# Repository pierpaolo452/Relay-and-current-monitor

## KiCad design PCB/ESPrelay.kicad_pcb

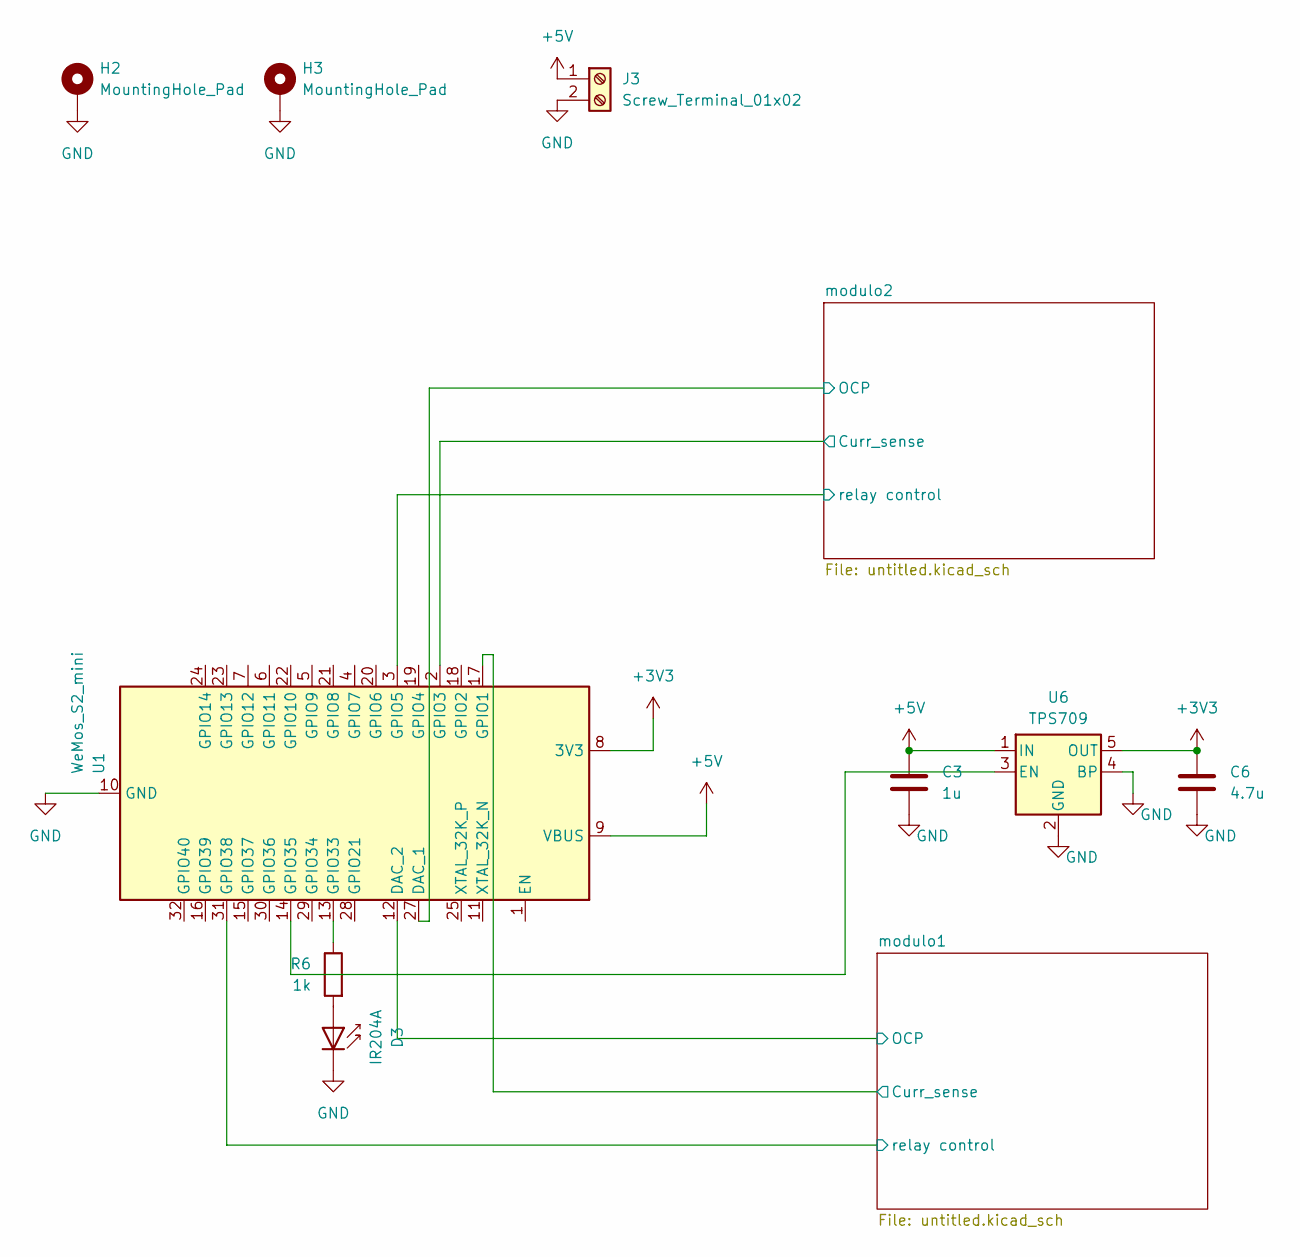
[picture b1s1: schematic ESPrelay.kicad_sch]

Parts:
C3: 1u; C_0805_2012Metric_Pad1.18x1.45mm_HandSolder
C6: 4.7u; C_0805_2012Metric_Pad1.18x1.45mm_HandSolder
D3: IR204A; LED_D3.0mm_Horizontal_O1.27mm_Z2.0mm_IRBlack
H2, H3: MountingHole_Pad; MountingHole_5.3mm_M5_Pad_Via
J3: Screw_Terminal_01x02; TerminalBlock_Phoenix_MKDS-3-2-5.08_1x02_P5.08mm_Horizontal
R6: 1k; R_0805_2012Metric
U1: WeMos_S2_mini; WEMOS_S2_mini
U6: TPS709; SOT-23-5_HandSoldering

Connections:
+3V3: C6.1, U1.8 (3V3), U6.5 (OUT); also elsewhere on the board
+5V: C3.1, J3.1, U1.9 (VBUS), U6.1 (IN); also elsewhere on the board
/modulo1/Curr_sense: U1.17 (GPIO1); also elsewhere on the board
/modulo1/OCP: U1.12 (DAC_2); also elsewhere on the board
/modulo1/relay control: U1.31 (GPIO38); also elsewhere on the board
/modulo2/Curr_sense: U1.2 (GPIO3); also elsewhere on the board
/modulo2/OCP: U1.27 (DAC_1); also elsewhere on the board
/modulo2/relay control: U1.3 (GPIO5); also elsewhere on the board
GND: C3.2, C6.2, D3.1 (K), H2.1, H3.1, J3.2, U1.10 (GND), U1.26 (GND), U6.2 (GND), U6.4 (BP); also elsewhere on the board
unnamed: D3.2 (A), R6.2
unnamed: R6.1, U1.13 (GPIO33)
unnamed: U1.14 (GPIO35), U6.3 (EN)

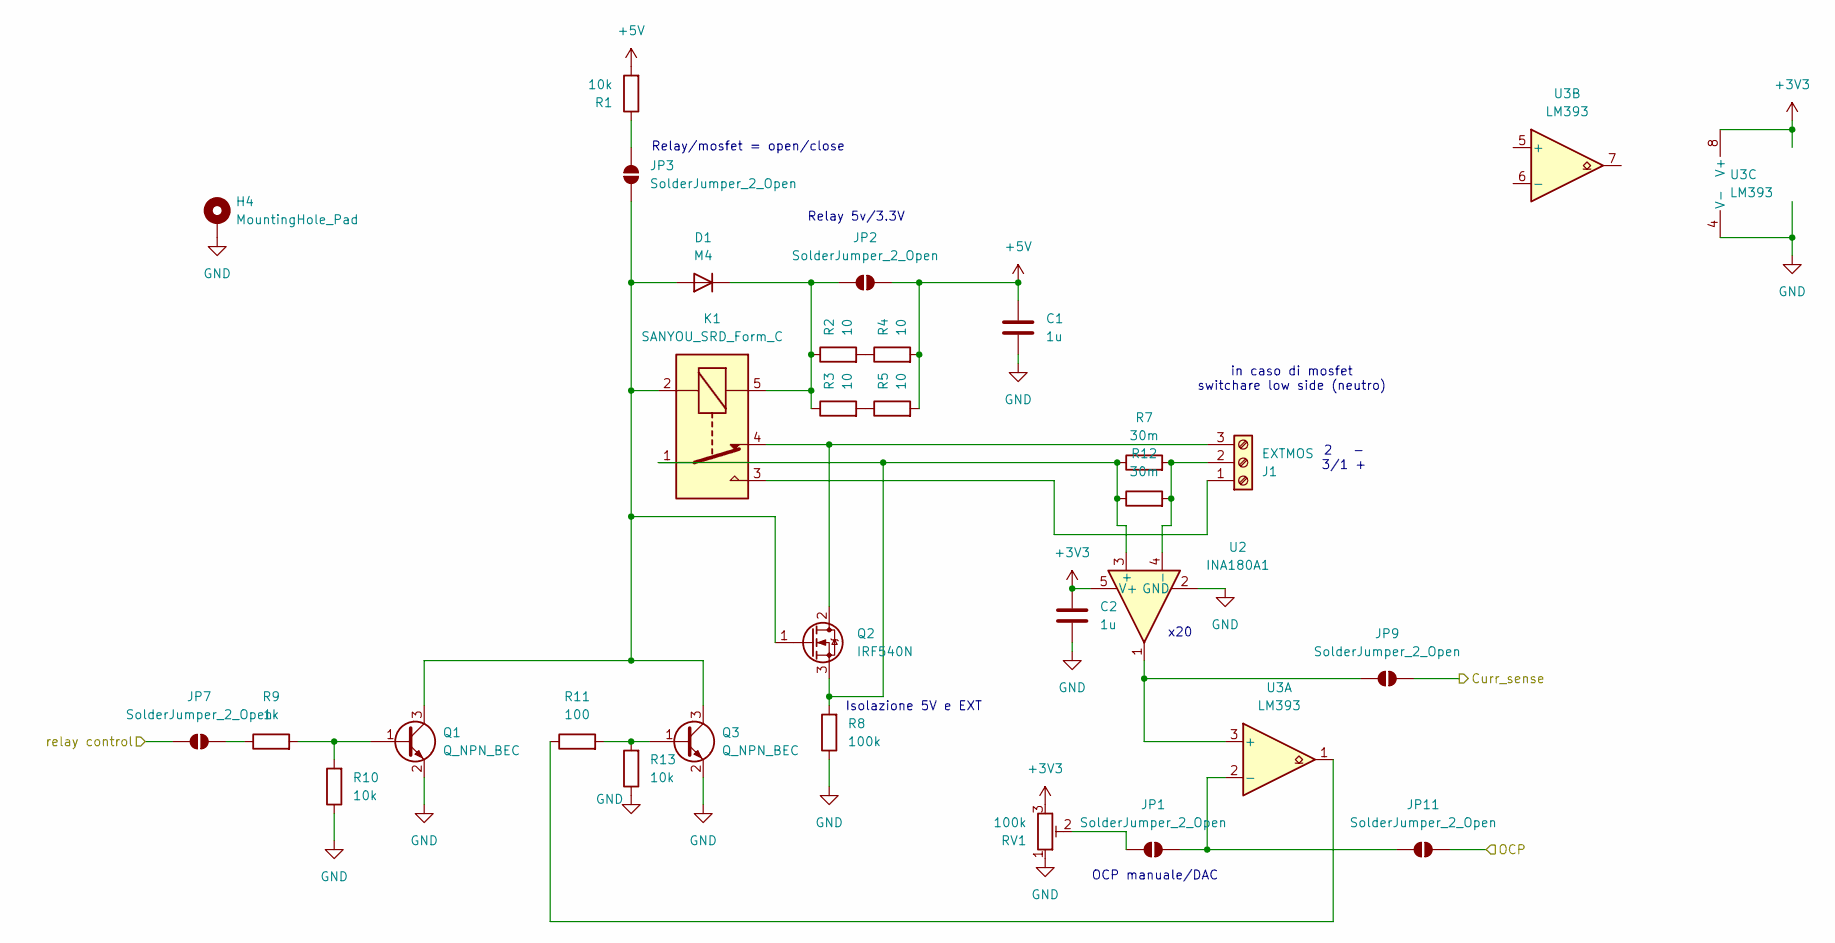
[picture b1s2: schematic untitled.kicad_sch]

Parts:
C1, C2: 1u; C_0805_2012Metric
D1: M4; D_SMA
H4: MountingHole_Pad; MountingHole_5.3mm_M5_Pad_Via
J1: EXTMOS; TerminalBlock_Phoenix_MKDS-1,5-3-5.08_1x03_P5.08mm_Horizont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
JP1, JP2, JP3, JP7, JP9, JP11: SolderJumper_2_Open; SolderJumper-2_P1.3mm_Open_RoundedPad1.0x1.5mm
K1: SANYOU_SRD_Form_C; Relay_SPDT_SANYOU_SRD_Series_Form_C
Q1, Q3: Q_NPN_BEC; SOT-23
Q2: IRF540N; TO-220-3_Vertical
R1, R10, R13: 10k; R_0805_2012Metric
R2, R3, R4, R5: 10; R_0805_2012Metric
R7, R12: 30m; R_2512_6332Metric_Pad1.40x3.35mm_HandSolder
R8: 100k; R_0805_2012Metric
R9: 1k; R_0805_2012Metric
R11: 100; R_0805_2012Metric
RV1: 100k; Potentiometer_ACP_CA9-H5_Horizontal; LCSC C118929
U2: INA180A1; SOT-23-5
U3: LM393; SOIC-8_3.9x4.9mm_P1.27mm

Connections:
+3V3: C2.1, RV1.3, U2.5 (V+), U3.8 (V+); also elsewhere on the board
+5V: C1.1, JP2.1 (A), R1.2, R4.2, R5.2; also elsewhere on the board
/modulo1/Curr_sense: JP9.1 (A); also elsewhere on the board
/modulo1/OCP: JP11.1 (A); also elsewhere on the board
/modulo1/relay control: JP7.2 (B); also elsewhere on the board
GND: C1.2, C2.2, H4.1, Q1.2 (E), Q3.2 (E), R8.1, R10.1, R13.1, RV1.1, U2.2 (GND), U3.4 (V-); also elsewhere on the board
unnamed: D1.2 (A), JP3.1 (A), K1.2, Q1.3 (C), Q2.1 (G), Q3.3 (C)
unnamed: D1.1 (K), JP2.2 (B), K1.5, R2.1, R3.1
unnamed: J1.1, K1.3
unnamed: J1.2, R7.2, R12.2, U2.4 (-)
unnamed: J1.3, K1.4, Q2.2 (D)
unnamed: JP1.1 (A), JP11.2 (B), U3.2 (-)
unnamed: JP1.2 (B), RV1.2
unnamed: JP3.2 (B), R1.1
unnamed: JP7.1 (A), R9.1
unnamed: JP9.2 (B), U2.1, U3.3 (+)
unnamed: Q1.1 (B), R9.2, R10.2
unnamed: K1.1, Q2.3 (S), R7.1, R8.2, R12.1, U2.3 (+)
unnamed: Q3.1 (B), R11.2, R13.2
unnamed: R2.2, R4.1
unnamed: R3.2, R5.1
unnamed: R11.1, U3.1

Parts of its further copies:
C4, C5: 1u; C_0805_2012Metric
D2: M4; D_SMA
H1: MountingHole_Pad; MountingHole_5.3mm_M5_Pad_Via
J2: EXTMOS; TerminalBlock_Phoenix_MKDS-1,5-3-5.08_1x03_P5.08mm_Horizont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
JP4, JP5, JP6, JP8, JP10, JP12: SolderJumper_2_Open; SolderJumper-2_P1.3mm_Open_RoundedPad1.0x1.5mm
K2: SANYOU_SRD_Form_C; Relay_SPDT_SANYOU_SRD_Series_Form_C
Q4, Q5: Q_NPN_BEC; SOT-23
Q6: IRF540N; TO-220-3_Vertical
R14: 1k; R_0805_2012Metric
R15, R17, R18: 10k; R_0805_2012Metric
R16: 100; R_0805_2012Metric
R19: 100k; R_0805_2012Metric
R20, R21, R22, R23: 10; R_0805_2012Metric
R24, R25: 30m; R_2512_6332Metric_Pad1.40x3.35mm_HandSolder
RV2: 100k; Potentiometer_ACP_CA9-H5_Horizontal; LCSC C118929
U4: INA180A1; SOT-23-5
U5: LM393; SOIC-8_3.9x4.9mm_P1.27mm

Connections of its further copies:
+3V3: C5.1, RV2.3, U4.5 (V+), U5.8 (V+); also elsewhere on the board
+5V: C4.1, JP5.1 (A), R17.2, R22.2, R23.2; also elsewhere on the board
/modulo2/Curr_sense: JP10.1 (A); also elsewhere on the board
/modulo2/OCP: JP12.1 (A); also elsewhere on the board
/modulo2/relay control: JP8.2 (B); also elsewhere on the board
GND: C4.2, C5.2, H1.1, Q4.2 (E), Q5.2 (E), R15.1, R18.1, R19.1, RV2.1, U4.2 (GND), U5.4 (V-); also elsewhere on the board
unnamed: D2.2 (A), JP4.1 (A), K2.2, Q4.3 (C), Q5.3 (C), Q6.1 (G)
unnamed: D2.1 (K), JP5.2 (B), K2.5, R20.1, R21.1
unnamed: J2.1, K2.3
unnamed: J2.2, R24.2, R25.2, U4.4 (-)
unnamed: J2.3, K2.4, Q6.2 (D)
unnamed: JP4.2 (B), R17.1
unnamed: JP6.2 (B), RV2.2
unnamed: JP8.1 (A), R14.1
unnamed: JP10.2 (B), U4.1, U5.3 (+)
unnamed: JP6.1 (A), JP12.2 (B), U5.2 (-)
unnamed: Q4.1 (B), R14.2, R15.2
unnamed: Q5.1 (B), R16.2, R18.2
unnamed: K2.1, Q6.3 (S), R19.2, R24.1, R25.1, U4.3 (+)
unnamed: R16.1, U5.1
unnamed: R20.2, R22.1
unnamed: R21.2, R23.1

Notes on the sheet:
x20
Isolazione 5V e EXT
in caso di mosfet switchare low side (neutro)
2 - 3/1 +
OCP manuale/DAC
Relay 5v/3.3V
Relay/mosfet = open/close

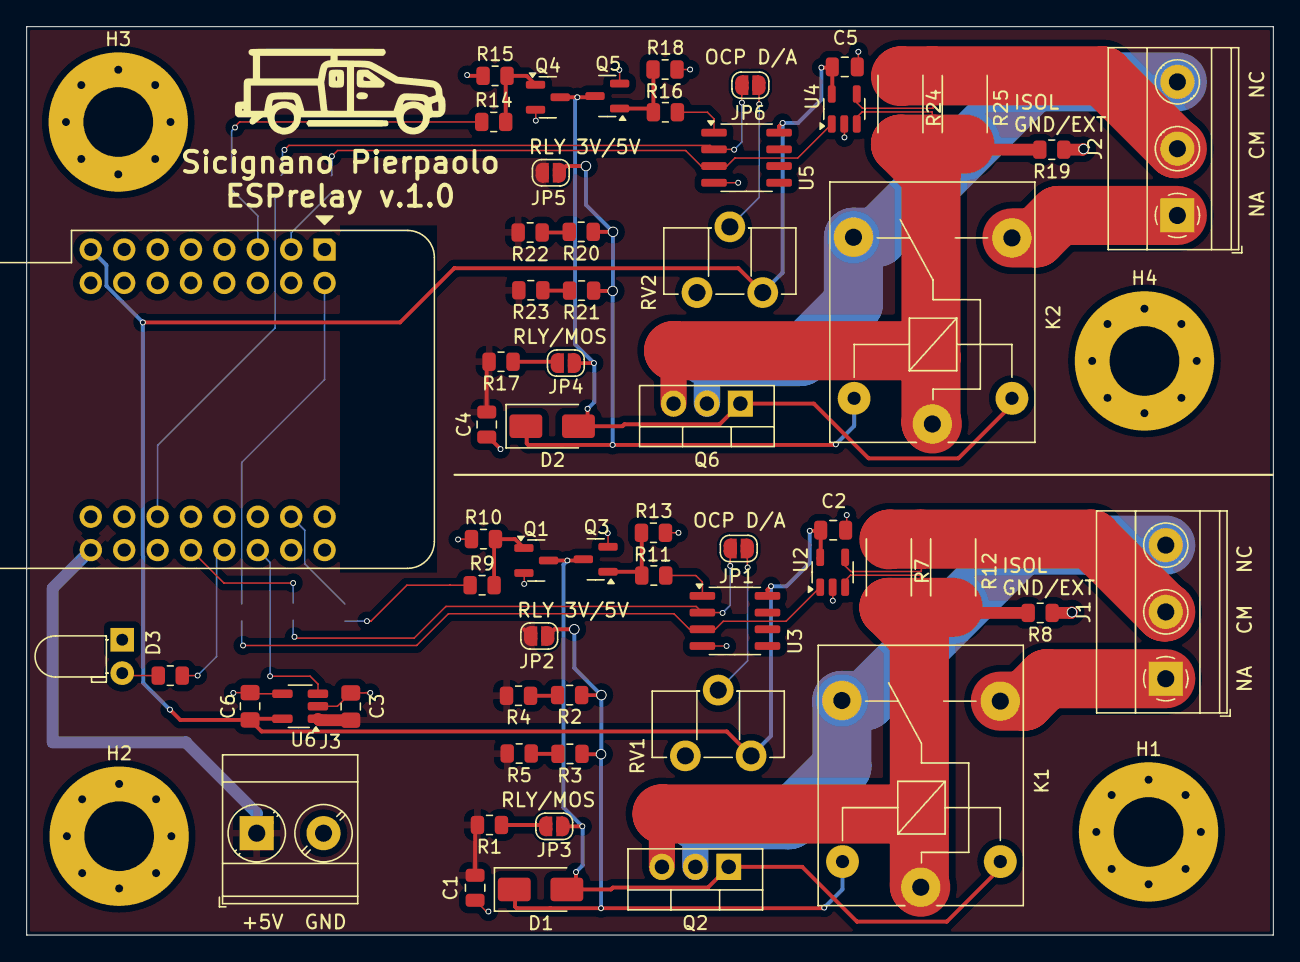
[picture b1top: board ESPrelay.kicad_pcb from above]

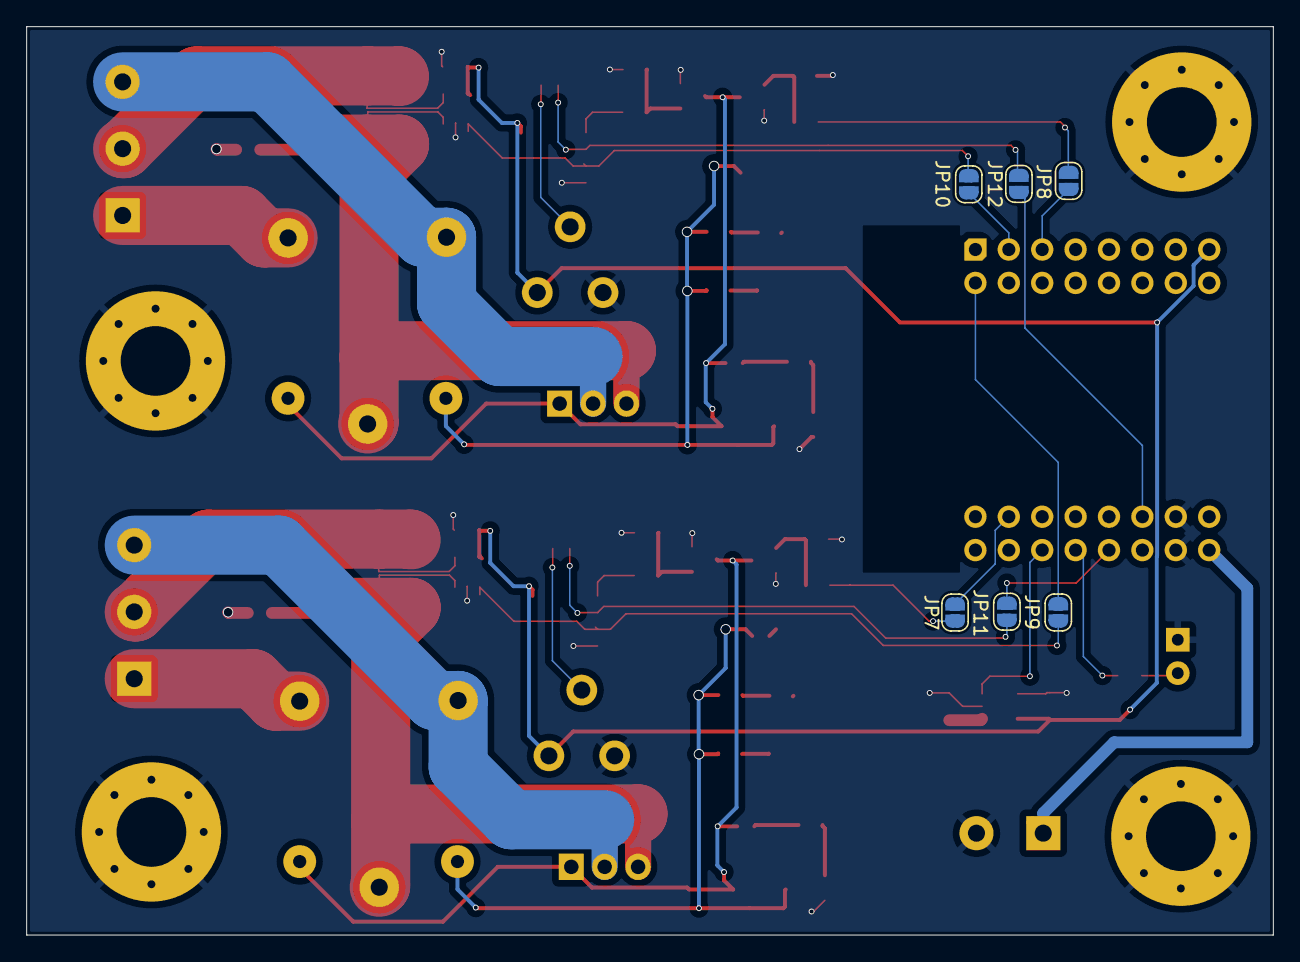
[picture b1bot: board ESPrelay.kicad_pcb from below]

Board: 2 copper layers, 94.8 x 69.1 mm, 69 parts (6 on the bottom side), 44 nets.

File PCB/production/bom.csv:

Designator,Footprint,Quantity,Value,LCSC Part #
"C1, C2, C3, C4, C5",0805,5,1u,
C6,0805,1,4.7u,
"D1, D2",D_SMA,2,M4,
D3,LED_D3.0mm_Horizontal_O1.27mm_Z2.0mm_IRBlack,1,IR204A,
"J1, J2","TerminalBlock_Phoenix_MKDS-1,5-3-5.08_1x03_P5.08mm_Horizontal",2,EXTMOS,
J3,TerminalBlock_Phoenix_MKDS-3-2-5.08_1x02_P5.08mm_Horizontal,1,Screw_Terminal_01x02,
"K1, K2",Relay_SPDT_SANYOU_SRD_Series_Form_C,2,SANYOU_SRD_Form_C,
"Q1, Q3, Q4, Q5",SOT-23,4,Q_NPN_BEC,
"Q2, Q6",TO-220-3_Vertical,2,IRF540N,
"R1, R10, R13, R15, R17, R18",0805,6,10k,
"R11, R16",0805,2,100,
"R12, R24, R25, R7",2512,4,30m,
"R14, R6, R9",0805,3,1k,
"R19, R8",0805,2,100k,
"R2, R20, R21, R22, R23, R3, R4, R5",0805,8,10,
"RV1, RV2",Potentiometer_ACP_CA9-H5_Horizontal,2,100k,C118929
U1,WEMOS_S2_mini,1,WeMos_S2_mini,
"U2, U4",SOT-23-5,2,INA180A1,
"U3, U5",SOIC-8_3.9x4.9mm_P1.27mm,2,LM393,
U6,SOT-23-5_HandSoldering,1,TPS709,
